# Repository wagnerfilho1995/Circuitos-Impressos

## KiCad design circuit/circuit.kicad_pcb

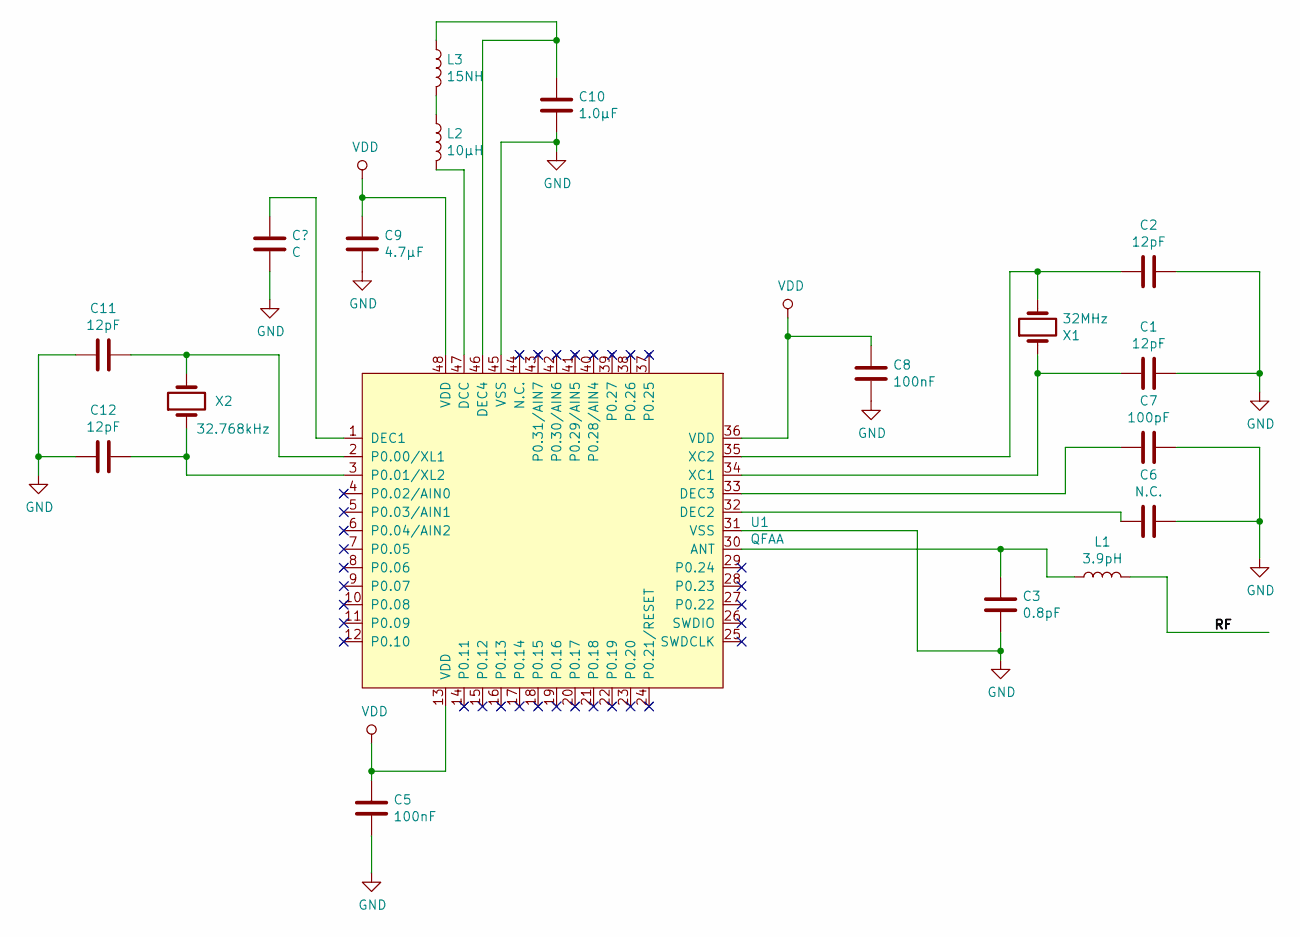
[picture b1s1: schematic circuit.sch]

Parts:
32MHz: X1
C1, C2, C11, C12: 12pF
C3: 0.8pF
C5, C8: 100nF
C6: N.C.
C7: 100pF
C9: 4.7µF
C10: 1.0µF
L1: 3.9pH
L2: 10µH
L3: 15NH
U1: QFAA
X2: 32.768kHz

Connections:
/RF: L1.2
GND: C1.1, C2.1, C3.2, C5.2, C6.1, C7.1, C8.2, C9.2, C10.2, C11.1, C12.1, U1.31 (VSS), U1.45 (VSS); also elsewhere on the board
unnamed 2: 32MHz.1, C1.2, U1.34 (XC1); also elsewhere on the board
unnamed 3: 32MHz.2, C2.2, U1.35 (XC2); also elsewhere on the board
unnamed: C3.1, L1.1, U1.30 (ANT)
unnamed 5: U1.1 (DEC1); also elsewhere on the board
unnamed: C6.2, U1.32 (DEC2)
unnamed: C7.2, U1.33 (DEC3)
unnamed: C10.1, L3.1, U1.46 (DEC4)
unnamed: C11.2, U1.2 (P0.00/XL1), X2.2
unnamed: C12.2, U1.3 (P0.01/XL2), X2.1
unnamed: L2.1, L3.2
unnamed: L2.2, U1.47 (DCC)
VDD: C5.1, C8.1, C9.1, U1.13 (VDD), U1.36 (VDD), U1.48 (VDD)

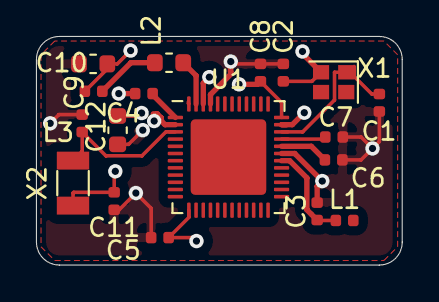
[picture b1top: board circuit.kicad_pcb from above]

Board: 2 copper layers, 20.3 x 12.7 mm, 18 parts (0 on the bottom side), 13 nets.

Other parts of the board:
C4: 100nF; C_0402_1005Metric
X1: 32MHz; Crystal_SMD_2016-4Pin_2.0x1.6mm

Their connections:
GND: C4.2; also elsewhere on the board
unnamed 2: X1.1; also elsewhere on the board
unnamed 3: X1.2; also elsewhere on the board
unnamed 5: C4.1; also elsewhere on the board

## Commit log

2019-06-05 Esquemático: nRF52832
    Primeira atividade da disciplina de Circuitos Impressos - 2019.1
    datasheet: https://infocenter.nordicsemi.com/pdf/nRF52832_PS_v1.0.pdf
2019-06-13 pcb layout
2019-06-28 Placa-01
2019-07-01 Continuação
2019-07-01 Esquematico
2019-07-22 Projeto pager - Revisão 03
    Quando fazer o download, lembrar de atualizar o caminho da custom.lib.
2019-07-28 Andamento do projeto
